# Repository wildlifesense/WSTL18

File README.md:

This repository was moved to https://github.com/NikosVallianos/NestProbe-TL1 due to project renaming and restructuring.

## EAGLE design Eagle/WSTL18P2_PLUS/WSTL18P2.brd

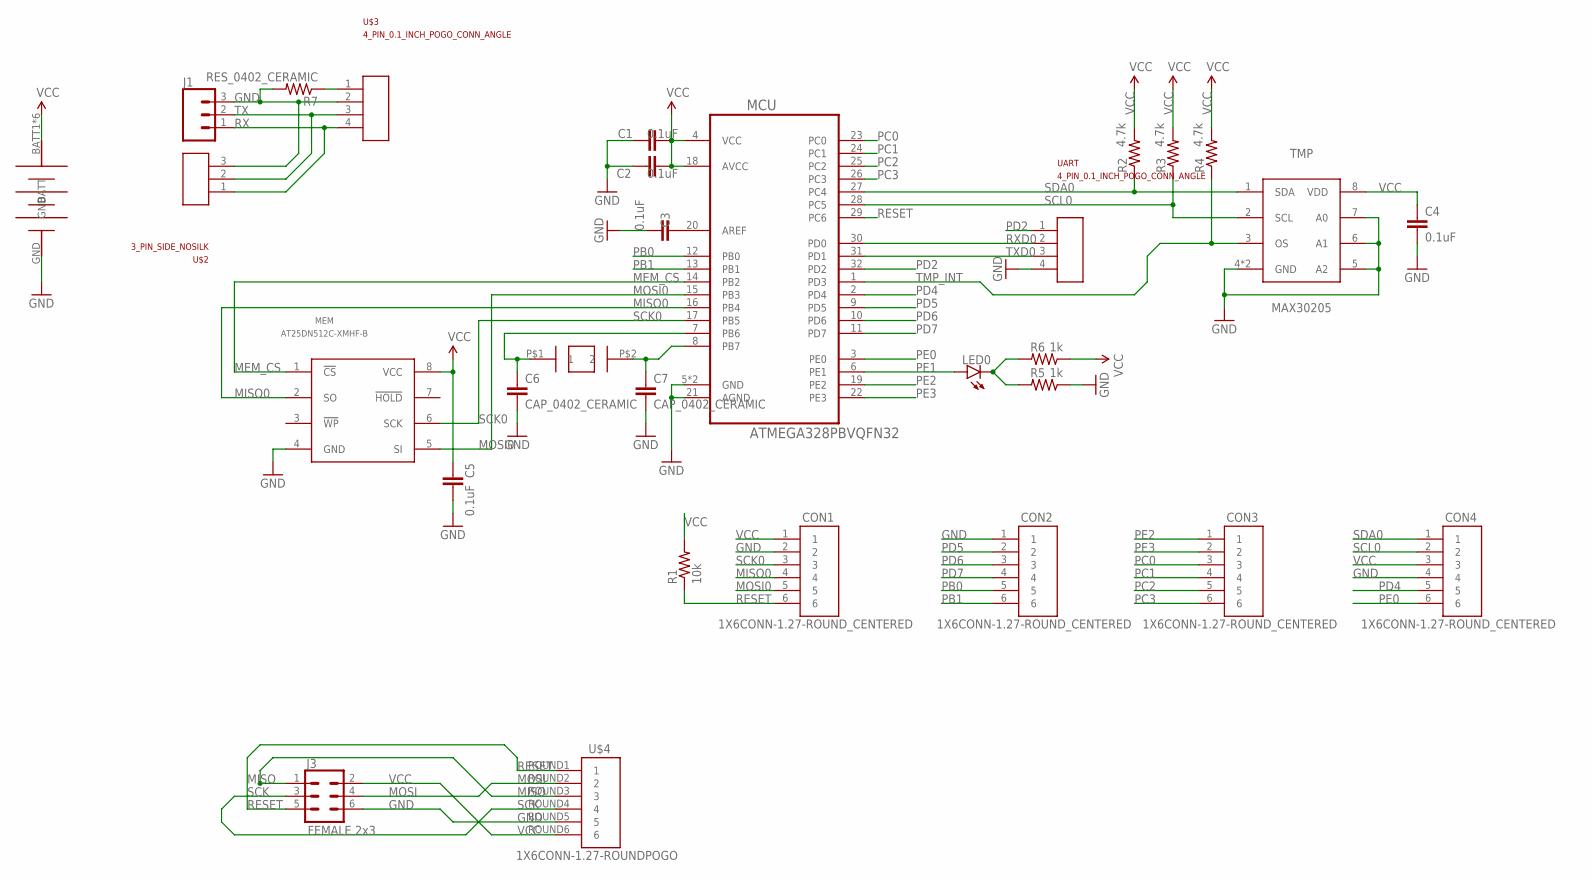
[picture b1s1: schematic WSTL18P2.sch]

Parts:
C1, C2, C3: 0.1uF; SMD_0402
C4, C5: 0.1uF; CAP_0402
C6, C7: CAP_0402_CERAMIC; CAP_0402
CON1, CON2, CON3, CON4: 1X6CONN-1.27-ROUND_CENTERED; 1X6_1.27_ROUND_CENTERED
J1: CONN_03; 1X03
J3: FEMALE 2x3; 2X3
LED0: LED_0402
MCU: ATMEGA328PBVQFN32; ATMEGA328PB_VFQFN32
MEM: AT25DN512C-XMHF-B; TSSSOP-8
R1: 10k; RES_0402
R2, R3, R4: 4.7k; RES_0402
R5, R6: 1k; RES_0402
R7: RES_0402_CERAMIC; RES_0402
T1: ABS07AIG
TMP: MAX30205; MAX30205_TDFN8
U$1: LINX-CR2032-BAT-HLD-M-THM; CR2032-LINX-M-THM
U$2: 3_PIN_SIDE_NOSILK; 3PIN_SIDE_0.1_INCH_NOSILK
U$3: 4_PIN_0.1_INCH_POGO_CONN_ANGLE; 4_PIN_0.1INCH_POGO_PADS_ANGLE
U$4: 1X6CONN-1.27-ROUNDPOGO; 1X6_1.27_SIDEPOGO
UART: 4_PIN_0.1_INCH_POGO_CONN_ANGLE; 4_PIN_0.1INCH_POGO_PADS_ANGLE

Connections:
AREF: C3.1, MCU.20 (AREF)
GND: C1.2, C2.2, C3.2, C4.2, C5.2, C6.2, C7.2, CON1.2, CON2.1, CON4.4, J1.3, J3.6, MCU.5 (GND), MCU.21 (AGND), MCU.PAD (GND), MEM.4 (GND), R5.2, R7.1, TMP.4 (GND), TMP.5 (A2), TMP.6 (A1), TMP.7 (A0), TMP.PAD (GND), U$1.GND, U$2.3, U$3.2, U$4.ROUND5 (5), UART.4
INT0: R7.2, U$3.1
MEM_CS: MCU.14 (PB2), MEM.1 (!CS!)
MISO: J3.1, U$4.ROUND3 (3)
MISO0: CON1.4, MCU.16 (PB4), MEM.2 (SO)
MOSI: J3.4, U$4.ROUND2 (2)
MOSI0: CON1.5, MCU.15 (PB3), MEM.5 (SI)
unnamed: C7.1, MCU.8 (PB7), T1.P$2 (2)
unnamed: C6.1, MCU.7 (PB6), T1.P$1 (1)
unnamed: LED0.CATHODE (C), R5.1, R6.1
PB0: CON2.5, MCU.12 (PB0)
PB1: CON2.6, MCU.13 (PB1)
PC0: CON3.3, MCU.23 (PC0)
PC1: CON3.4, MCU.24 (PC1)
PC2: CON3.5, MCU.25 (PC2)
PC3: CON3.6, MCU.26 (PC3)
PD2: MCU.32 (PD2), UART.1
PD4: CON4.5, MCU.2 (PD4)
PD5: CON2.2, MCU.9 (PD5)
PD6: CON2.3, MCU.10 (PD6)
PD7: CON2.4, MCU.11 (PD7)
PE0: CON4.6, MCU.3 (PE0)
PE1: LED0.ANODE (A), MCU.6 (PE1)
PE2: CON3.1, MCU.19 (PE2)
PE3: CON3.2, MCU.22 (PE3)
RESET: CON1.6, J3.5, MCU.29 (PC6), R1.2, U$4.ROUND1 (1)
RX: J1.1, U$2.1, U$3.4
RXD0: MCU.30 (PD0), UART.2
SCK: J3.3, U$4.ROUND4 (4)
SCK0: CON1.3, MCU.17 (PB5), MEM.6 (SCK)
SCL0: CON4.2, MCU.28 (PC5), R3.2, TMP.2 (SCL)
SDA0: CON4.1, MCU.27 (PC4), R2.2, TMP.1 (SDA)
TMP_INT: MCU.1 (PD3), R4.2, TMP.3 (OS)
TX: J1.2, U$2.2, U$3.3
TXD0: MCU.31 (PD1), UART.3
VCC: C1.1, C2.1, C4.1, C5.1, CON1.1, CON4.3, J3.2, MCU.4 (VCC), MCU.18 (AVCC), MEM.8 (VCC), R1.1, R2.1, R3.1, R4.1, R6.2, TMP.8 (VDD), U$1.BATT1 (BATT), U$1.BATT2 (BATT), U$1.BATT3 (BATT), U$1.BATT4 (BATT), U$1.BATT5 (BATT), U$1.BATT6 (BATT), U$4.ROUND6 (6)

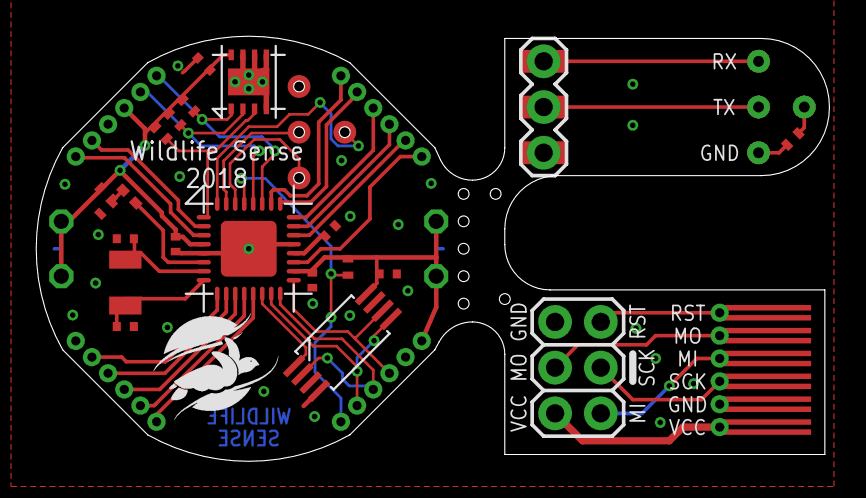
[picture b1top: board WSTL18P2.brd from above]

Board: 2 copper layers, 44.1 x 23.6 mm, 30 parts (1 on the bottom side), 37 nets.

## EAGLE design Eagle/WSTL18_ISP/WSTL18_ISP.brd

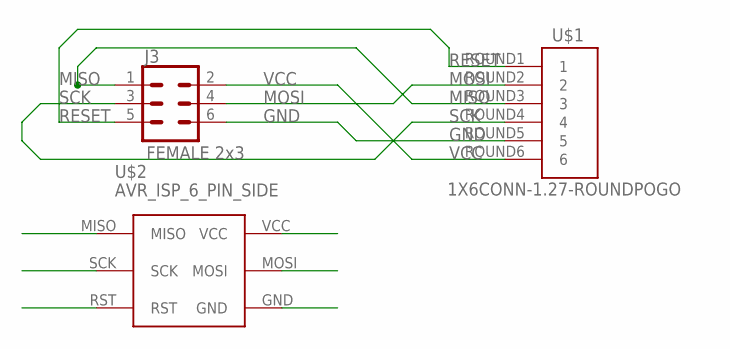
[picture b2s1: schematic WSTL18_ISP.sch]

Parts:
J3: FEMALE 2x3; 2X3
U$1: 1X6CONN-1.27-ROUNDPOGO; 1X6_1.27_SIDEPOGO
U$2: AVR_ISP_6_PIN_SIDE; AVR_ISP_SIDE_0.1_INCH

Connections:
GND: J3.6, U$1.ROUND5 (5), U$2.GND
MISO: J3.1, U$1.ROUND3 (3), U$2.MISO
MOSI: J3.4, U$1.ROUND2 (2), U$2.MOSI
RESET: J3.5, U$1.ROUND1 (1), U$2.RST
SCK: J3.3, U$1.ROUND4 (4), U$2.SCK
VCC: J3.2, U$1.ROUND6 (6), U$2.VCC

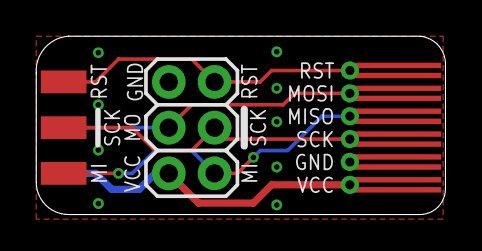
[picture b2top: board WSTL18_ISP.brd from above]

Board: 2 copper layers, 22.7 x 9.9 mm, 3 parts (0 on the bottom side), 6 nets.

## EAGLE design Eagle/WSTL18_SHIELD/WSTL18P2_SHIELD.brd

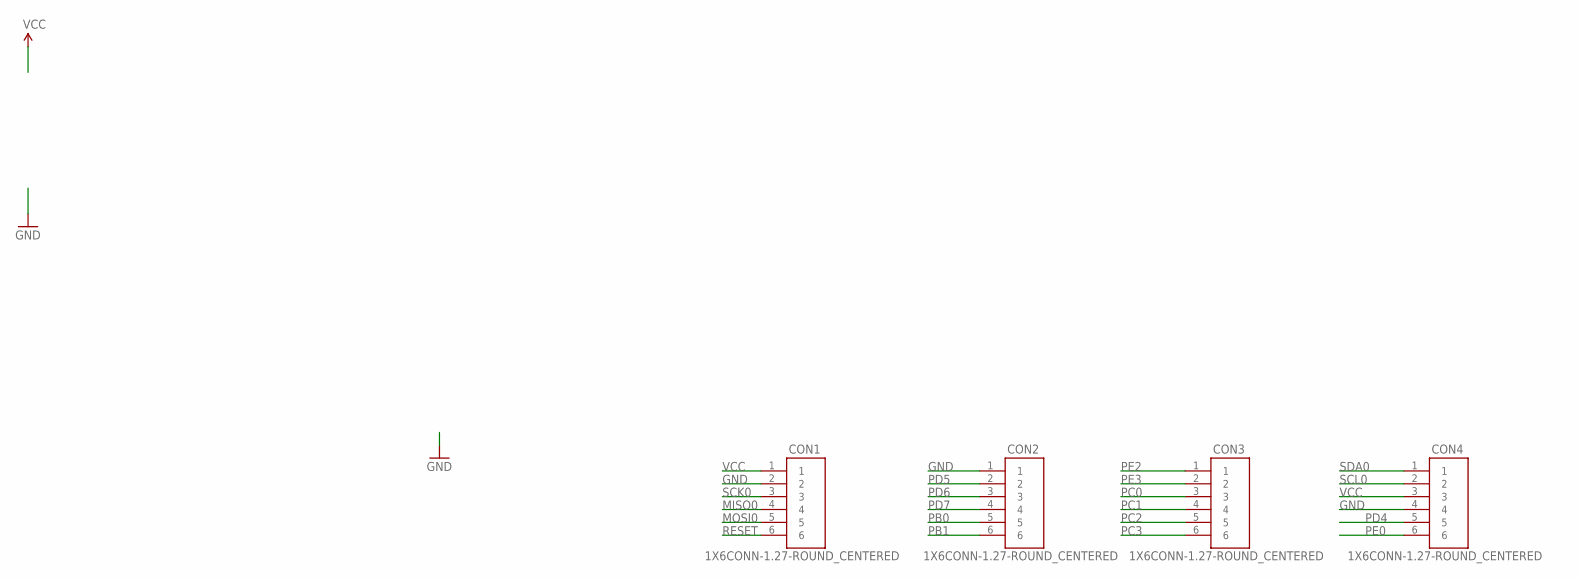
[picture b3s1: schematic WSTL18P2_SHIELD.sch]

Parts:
CON1, CON2, CON3, CON4: 1X6CONN-1.27-ROUND_CENTERED; 1X6_1.27_ROUND_CENTERED

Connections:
GND: CON1.2, CON2.1, CON4.4
MISO0: CON1.4
MOSI0: CON1.5
PB0: CON2.5
PB1: CON2.6
PC0: CON3.3
PC1: CON3.4
PC2: CON3.5
PC3: CON3.6
PD4: CON4.5
PD5: CON2.2
PD6: CON2.3
PD7: CON2.4
PE0: CON4.6
PE2: CON3.1
PE3: CON3.2
RESET: CON1.6
SCK0: CON1.3
SCL0: CON4.2
SDA0: CON4.1
VCC: CON1.1, CON4.3

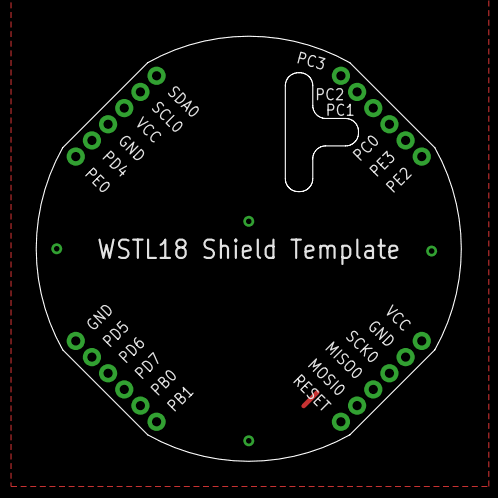
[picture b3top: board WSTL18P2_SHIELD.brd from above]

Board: 2 copper layers, 23.6 x 23.6 mm, 4 parts (0 on the bottom side), 2 nets.

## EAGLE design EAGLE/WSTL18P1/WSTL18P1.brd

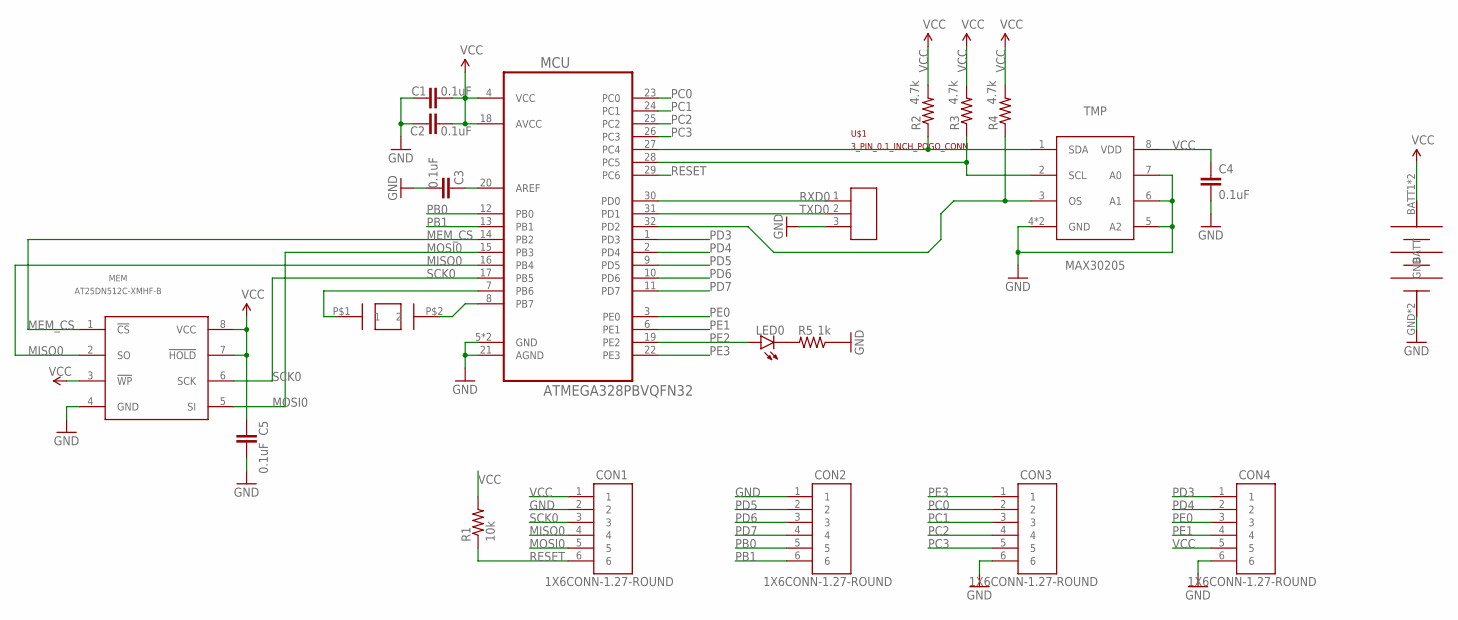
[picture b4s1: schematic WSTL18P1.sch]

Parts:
BAT: LINX-CR2032-BAT-HLD-001-M; CR2032-LINX-M
C1, C2, C3, C4, C5: 0.1uF; CAP_0402
CON1, CON2, CON3, CON4: 1X6CONN-1.27-ROUND; 1X6_1.27_ROUND
LED0: LED_0402
MCU: ATMEGA328PBVQFN32; ATMEGA328PB_VFQFN32
MEM: AT25DN512C-XMHF-B; TSSSOP-8
R1: 10k; RES_0402
R2, R3, R4: 4.7k; RES_0402
R5: 1k; RES_0402
T1: ABS07AIG
TMP: MAX30205; MAX30205_TDFN8
U$1: 3_PIN_0.1_INCH_POGO_CONN; 3_PIN_0.1INCH_POGO_PADS

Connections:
GND: BAT.GND, BAT.GND1 (GND), C1.2, C2.2, C3.2, C4.2, C5.2, CON1.2, CON2.1, CON3.6, CON4.6, MCU.5 (GND), MCU.21 (AGND), MCU.PAD (GND), MEM.4 (GND), R5.2, TMP.4 (GND), TMP.5 (A2), TMP.6 (A1), TMP.7 (A0), TMP.PAD (GND), U$1.3
MEM_CS: MCU.14 (PB2), MEM.1 (!CS!)
MISO0: CON1.4, MCU.16 (PB4), MEM.2 (SO)
MOSI0: CON1.5, MCU.15 (PB3), MEM.5 (SI)
unnamed: MCU.8 (PB7), T1.P$2 (2)
unnamed: MCU.7 (PB6), T1.P$1 (1)
unnamed: C3.1, MCU.20 (AREF)
unnamed: LED0.CATHODE (C), R5.1
PB0: CON2.5, MCU.12 (PB0)
PB1: CON2.6, MCU.13 (PB1)
PC0: CON3.2, MCU.23 (PC0)
PC1: CON3.3, MCU.24 (PC1)
PC2: CON3.4, MCU.25 (PC2)
PC3: CON3.5, MCU.26 (PC3)
PD3: CON4.1, MCU.1 (PD3)
PD4: CON4.2, MCU.2 (PD4)
PD5: CON2.2, MCU.9 (PD5)
PD6: CON2.3, MCU.10 (PD6)
PD7: CON2.4, MCU.11 (PD7)
PE0: CON4.3, MCU.3 (PE0)
PE1: CON4.4, MCU.6 (PE1)
PE2: LED0.ANODE (A), MCU.19 (PE2)
PE3: CON3.1, MCU.22 (PE3)
RESET: CON1.6, MCU.29 (PC6), R1.2
RXD0: MCU.30 (PD0), U$1.1
SCK0: CON1.3, MCU.17 (PB5), MEM.6 (SCK)
SCL0: MCU.28 (PC5), R3.2, TMP.2 (SCL)
SDA0: MCU.27 (PC4), R2.2, TMP.1 (SDA)
TMP_INT: MCU.32 (PD2), R4.2, TMP.3 (OS)
TXD0: MCU.31 (PD1), U$1.2
VCC: BAT.BATT1 (BATT), BAT.BATT2 (BATT), C1.1, C2.1, C4.1, C5.1, CON1.1, CON4.5, MCU.4 (VCC), MCU.18 (AVCC), MEM.3 (!WP!), MEM.7 (!HOLD!), MEM.8 (VCC), R1.1, R2.1, R3.1, R4.1, TMP.8 (VDD)

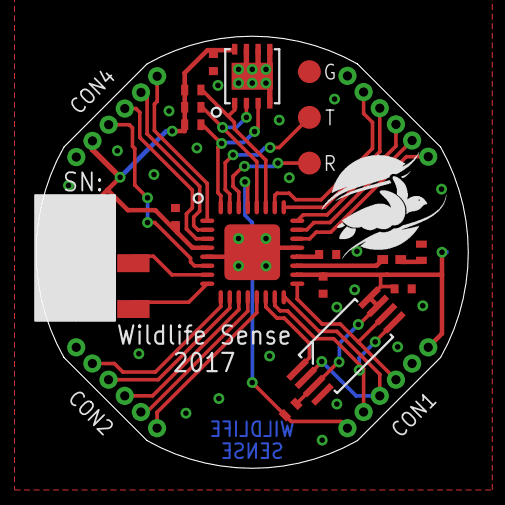
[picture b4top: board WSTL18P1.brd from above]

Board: 2 copper layers, 24.0 x 24.0 mm, 21 parts (1 on the bottom side), 31 nets.

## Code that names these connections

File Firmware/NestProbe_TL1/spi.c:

/********************************************************************************

  spi.c: SPI module of WSTL18 firmware.
 
  Copyright (C) 2017 Nikos Vallianos <nikos@wildlifesense.com>
  
  This file is part of WSTL18 firmware.
  
  WSTL18 firmware is free software: you can redistribute it and/or modify
  it under the terms of the GNU General Public License as published by
  the Free Software Foundation, either version 3 of the License, or
  (at your option) any later version.
  
  WSTL18 firmware is distributed in the hope that it will be useful,
  but WITHOUT ANY WARRANTY; without even the implied warranty of
  MERCHANTABILITY or FITNESS FOR A PARTICULAR PURPOSE.  See the
  GNU General Public License for more details.
  
  You should have received a copy of the GNU General Public License
  in the file COPYING along with this program.  If not,
  see <http://www.gnu.org/licenses/>.

  ********************************************************************************/
#include <avr/io.h>
#include <avr/interrupt.h>
#include "spi.h"

// #################### PORTS & PINS FOR SPI0. Don't change unless porting to another mcu ####################
//	MISO0 is PB4
//	SCK0 is PB5
//	MOSI0 is PB3
//	SS0 is PB2

// Initialize pins for spi communication
void spiEnable(void) {
	DDRB &= ~(1<<DDRB4);		// MISO is INPUT
	PORTB &= ~(1<<PORTB4);		// No pull (tri-state for inputs?)
	
	DDRB |= (1<<DDRB3);			// MOSI output
	PORTB &= ~(1<<PORTB3);		// Low

	DDRB |= (1<<DDRB5);			// SCK out
	PORTB &= ~(1<<PORTB5);		// Low

    PRR0 &= ~(1<<PRSPI0);								// Clock SPI0 clock, powers the module
	
	SPCR0 = (1<<SPE) | (1<<MSTR) | (0<<SPR1) | (0<<SPR0);		// Enable SPI, set to Master, set prescaler.
}

/*
 * spiDisable: Disable the SPI module and set it for lowest power consumption.
 * TODO: Add some fault detection: SPSR0.WCOL0
 */
void spiDisable(void) {
	SPCR0 = 0;											// Disable SPI.
	PRR0 |= (1<<PRSPI0);								// Cut off SPI0 clock, shuts the module	
	DDRB  &= ~(1<<DDRB3|1<<DDRB4|1<<DDRB5);				// MOSI0, SCK0, MISO0 pins are input
	PORTB |=  (1<<PORTB3|1<<PORTB4|1<<PORTB5);			// Pull-up enabled, reduces consumption.
}

// When a serial transfer is complete, the SPIF flag is set.
uint8_t spiTradeByte(uint8_t byte) {
	SPDR0 = byte;										
	loop_until_bit_is_set(SPSR0, SPIF);			
	return SPDR0;
}



// Shift an array out and retain returned data.
void spiExchangeArray(uint8_t * dataout, uint8_t * datain, uint8_t len) {
	for (uint8_t i = 0; i < len; i++) {
		datain[i] = spiTradeByte(dataout[i]);
	}
}



// Shift an array out and discard returned data.
void spiTransmitArray(uint8_t * dataout, uint8_t len) {
	for (uint8_t i = 0; i < len; i++) {
		spiTradeByte(dataout[i]);
	}
}

// Shift an array in while sending scrap data
void spiReceiveArray(uint8_t * datain, uint8_t len) {
	for (uint8_t i=0; i<len; i++) {
		datain[i] = spiTradeByte(0x00);
	}
}

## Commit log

2017-12-23 Added main.c
2017-12-23 Added COPYING file go repo
2017-12-23 Moved COPYING to main folder
2017-12-23 Added led module
2017-12-23 Added max30205 module
2017-12-23 Added memory module
2017-12-23 Added real time counter module
2017-12-23 Added spi, twi, uart, and wstl18 modules
2017-12-23 Created README.md
    Added a readme file to appear as this project's description.
2017-12-23 Added one line
2017-12-23 Added WSTL18.componentinfo file
2017-12-24 Added Atmel studio project files
2017-12-24 Added dia flow diagram files (dia and pdf)
2017-12-24 Added copyright/license notice
2017-12-24 Added details about the project
2017-12-24 Added .epf to .gitignore
2017-12-24 Added eagle design files
2017-12-24 Added a blank line
2017-12-24 Removed email from README
2017-12-24 Removed blank line
2017-12-24 Renamed EAGLE folder into Eagle
2017-12-24 Moved all firmware-related files into Firmware/
2017-12-24 Adding 1.27mm headers to TWI (I2C) lines.
    This will make the TWI accessible to expansion shields.
2017-12-24 Reducing signal trace widths towards 6mil
2017-12-24 Added a warning for WSTL18P2 eagle files
2017-12-24 Changing signal traces to 6 mil
2017-12-25 More routing optimizations and changing trances to 6 mil.
2017-12-25 Mostly adding comments in the MAX30205 module
2017-12-25 Some reorganization
2017-12-25 Reviewing in the memory module
2017-12-26 Added a battery module
2017-12-26 Removed battery module. Will add when core function done
2017-12-29 Minor tweaks in memory module
2017-12-30 Making TWI (I2C) pins available on perimeter headers
2018-01-02 Made TWI (I2C) available on perimeter 1.27mm headers
2018-01-03 More work on TWI (I2C) traces
2018-01-03 Work on the memory functions to record a temperature log
2018-01-03 Added pads on the positive battery holder contacts
    This will allow use of both SMD and through-hole versions of the battery holder
2018-01-03 Moved battery GND pad to a sincle circular in centre
2018-01-03 Reverted some passives back to 0402 size
2018-01-03 Updated README to include Eagle files
2018-01-03 Removed WP and HOLD connections to VCC on EEPROM
    Chip has internal pull-ups for when WP and HOLD functions are not used
2018-01-03 Rerouted TWI (I2C)
2018-01-04 Eliminated all 0201 passives, changed uart connection pin
2018-01-04 Chaned LED pin, added VCC and GND next to TWI(I2C) headers, changed some traces to 8mil
2018-01-05 Changing some traces up to 8 mils where space is available
2018-01-05 Final corrections for WSTL18P2
2018-01-06 Approved and cleared design rules checks
2018-01-07 Made a wstl18DoubleBlink function and moved it to wstl18.c
2018-01-07 Added a couple of notes for power reduction
2018-01-07 Minor port bit reference correction
2018-01-07 Corrected to DDR instead of PIN which wouldn't have worked
2018-01-07 Updates on project setup
2018-01-07 Comment-pasted working init code from older project for ideas
2018-01-07 Added sleep instructions, blinker, and uart functions
2018-01-07 Just a little comment
2018-01-07 Trying different configurations during code tests
2018-01-07 Added ISP connector eagle files
2018-01-07 Removed gerber files
2018-01-08 Finished design of WSTL18 in-system programming adaptor
2018-01-08 Center-alligned all 4 6-wire headers
2018-01-08 Added WSTL18 template shield eagle files
2018-01-09 Debugging for power consumption and operation
2018-01-11 Corrected board title layer
2018-01-12 Simplifying uart library
2018-01-12 Simplifying TWI initialization
2018-01-12 Streamlined the spi module
2018-01-13 TWI module works
2018-01-13 Test operation in main loop
2018-01-13 Temperature sensor seems to work like this
2018-01-13 Minor correction attempts
2018-01-13 Testing changes in initialization function
2018-01-13 Testing changes in memory module
2018-01-13 Minor modifications
2018-01-13 Added in-system programming adaptor
2018-01-16 Fixed speed-limiting initialization errors
2018-01-16 Restructuring TWI module to introduce error checking
2018-01-24 Fixed uart disable to allow minor delay
    This is an undocumented issue with seldom reporting in the community:
    If the device goes to sleep righ after something has been sent over uart,
    the AVR's uart buffers get messed up and remain so even when the uart is
    powered off before sleep and then on again after wakeup. The datasheet
    says that the TXC register must be checked, but even when it is the
    buffers still get messed up. The only viable solution was to add a
2018-01-24 Fixing TWI STOP bug
    Apparently, when the AVR sets the stop condition on the TWI lines,
    you don't have to wait for the TWINT flag. If you do, you'll never
    get it, which makes the entire program hang. The stop condition
    doesn't affect any buffers, so there's no need to wait. Just set the
    stop condition and leave.
2018-01-28 Too many fixes to list
2018-01-28 Added WSTL18P2 eagle with uart and ISP adaptors
2018-01-28 Added eagle files for UART adaptor
2018-01-28 Added host computer serial interface script
2018-01-28 Renamed UserProgram to Host
2018-01-28 Changed WSTL18.dia to WSTL18_Firmware.dia
2018-01-28 Added host program diagram
2018-01-29 Updates to protocol and program
2018-02-04 Reflects change in local version of Atmel Software Framework
2018-02-04 Reflects local change in Atmel Software Framework
2018-02-04 Testing communication with WSTL18 host computer program
2018-02-04 Updates in dia diagram (can't remember what)
2018-02-07 Removed led.c and led.h
2018-02-07 Removed wstl18 module
2018-02-20 Removed a couple of diagrams to reorganize them
2018-02-21 Added indicator module for LE Please enter the commit message for your changes. Lines starting
2018-02-21 Added an error tracking module
2018-02-21 Consolidating a couple of loose modules into main.c
2018-02-26 Reorganized, debugged memoryScan() to work
2018-02-26 Moved ISR out of rtc module and into main (for now)
2018-02-26 General update and development
2018-03-08 Updates to firmware
2018-03-08 Renamed a bunch of files to new name

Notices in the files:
parts and their libraries:
SparkFun-Aesthetics: Licensing: Creative Commons ShareAlike 4.0 International - https://creativecommons.org/licenses/by-sa/4.0
